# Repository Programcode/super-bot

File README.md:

# Super bot

Super bot (temporary working name) is Adam's passion-project home robot: an indoor mecanum-wheel robot with a creature-style head on a neck (think WALL-E or Vector), a translucent smoked shell, and a layered AI brain that can see, map, talk, fetch, remember, and teach itself new skills.

> **Master page:** the single source of truth is the Grok Bot page **"Super bot"** in Adam's Grok Bot library:
> https://cursor.com/canvas/store-3f866d4b-6e7e-4115-b119-325492ec6c21/45200f5a-d70f-476f-988f-23a206c0bfd9
> (opens for Adam's signed-in account; canvas id `45200f5a-d70f-476f-988f-23a206c0bfd9`).
> A markdown snapshot lives in [`docs/super-bot-page.md`](docs/super-bot-page.md). Pip re-syncs it whenever the page changes.

## Current status (17 Nov 2026)

- **Roadmap layer:** 1 of 6, "Brain on a desk" (laptop + webcam, local YOLO, Qwen mind, Whisper + Piper).
- **Body design:** exploring. AI concept renders are in [`docs/concepts/`](docs/concepts/). Current pick is concept K (WALL-E-style head on a neck, smoked translucent shell).
- **CAD:** starting in Autodesk Fusion. Fusion runs on Adam's Mac; Claude Code on the VPS drives it through Fusion's official MCP server over an SSH tunnel. See [`cad/`](cad/) and the Fusion section of [`CLAUDE.md`](CLAUDE.md).
- **Hardware:** parts plan agreed, mostly not bought yet. Adam owns a Pi 5 8 GB, an ELEGOO UNO kit, and a Circuit Playground Express. No ESP32-S3s yet.
- **Brain:** architecture drafted (mind / controller / reflexes). A full brain plan from Claude Fable is pending review.

Key decisions are in [`docs/decisions.md`](docs/decisions.md).

## The robot in one table

| Part | Plan |
| --- | --- |
| Drive | 80 mm mecanum wheels, 4× JGB37 12 V encoder gear motors, 4× BTS7960 drivers |
| Chassis | Cheap DIY 40×40 cm plate (plywood or aluminium), enclosed in a dense smoked translucent shell |
| Onboard brain | Raspberry Pi 5 8 GB, plus Raspberry Pi AI HAT+ 2 (Hailo-10H) later |
| Real-time | 2× ESP32-S3 (reflexes, motor control at ~1 kHz) |
| Sensors | BNO085 IMU, HC-SR04 ultrasonics, VL53L0X ToF, Logitech C270 webcam, mic |
| Face | 1.3" TFT face on the head |
| Status ring | Circuit Playground Express (10 NeoPixels), also backup tilt / safety |
| Power | 3S 18650 pack |
| Later | Cheap lidar (LD06 / LD19), arm, self-docking charger, custom PCB (v2, KiCad + JLCPCB) |

## Repo layout

```
.
├── CLAUDE.md              Project context for Claude Code (AGENTS.md points here)
├── docs/
│   ├── super-bot-page.md  Snapshot of the Grok Bot master page
│   ├── decisions.md       Decision log (keep current)
│   ├── sync.md            How the page snapshot is kept in sync
│   └── concepts/          AI concept renders (not real photos)
├── cad/                   Fusion designs, STEP/STL exports, Fusion API scripts
├── firmware/
│   ├── esp32/             ESP32-S3 reflex + motor firmware (PlatformIO)
│   └── cpx/               Circuit Playground Express status ring / backup safety
├── pi/                    Onboard brain (Python, later ROS 2)
├── electronics/           Wiring diagrams, future KiCad PCB
├── tests/benchmarks/      Mind benchmarks and test suites
└── scripts/               Helper scripts (ask-pip.sh, sync notes)
```

## License

MIT, see [LICENSE](LICENSE).

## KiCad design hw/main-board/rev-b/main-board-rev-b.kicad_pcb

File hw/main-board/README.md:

# Super bot main board, rev A

The main power and I/O carrier for Super bot v2: one 4-layer board that takes the battery, protects and measures it, makes every supply rail, drives the four wheels, and connects the Raspberry Pi 5 to everything else. The ESP32-S3 on it runs the motor and sensor reflexes. Designed in KiCad 10 on the VPS on 17-18 Nov 2026 by a Claude thread while Adam slept. Nothing has been ordered.

**Status (18 Nov 2026, 05:20 UTC): routed and checked.**
- **ERC:** 0.
- **DRC:** 0 violations and 0 unconnected items, with schematic parity 0. This is the full `kicad-check` gate: severity-all (warnings count), zones refilled, against JLC-safe rules (0.15 mm clearance, 0.10 mm minimum track, 0.3 mm minimum drill, 0.25 mm copper to edge).
- **Two project settings differ from KiCad's defaults:**
  - `lib_footprint_mismatch` is set to ignore, because silkscreen is trimmed per footprint.
  - Minimum thermal-relief spokes is 1 instead of 2, for fine-pitch GND pads in pours.
- **Fab set:** the JLCPCB outputs, STEP and renders are in `out/` and `renders/`.

Read **Open questions** before ordering. The outline is provisional, and three rev A compromises are listed there.

## What's on it

- **Battery input:** XT60 (battery) → 15 A blade fuse → XT30 loop for the DC main switch (or loop key) → reverse-polarity P-MOSFET → 2 mΩ shunt → 12 V bus. TVS on the bus.
- **Battery monitor:** INA226 (I2C 0x40), 16 A full scale, for the time-left model and limp mode.
- **Hardware motor cut (no button):** a retriggerable one-shot only keeps the motors powered while the ESP32 keeps toggling a watchdog pin. An open kill loop or the CPX kill line cuts them too. The cut does two things: it puts all four drivers to sleep and switches off the motor supply with a high-side P-MOSFET.
- **Motors:** 4× DRV8874 in PWM mode. Each limits current at 3.1 A and reports it to an ESP32 ADC (0.82 V/A), and each has an encoder input with pull-ups and RC filters.
- **Rails:**
  - 5.0 V / 6 A for the Pi 5 and 5 V loads (TPS56637), out through a USB-C port.
  - 5.5 V / 6 A servo rail on its own TPS56637.
  - 3.3 V / 1 A logic (AMS1117), which also runs from the ESP32's USB port so you can flash with the battery off.
- **ESP32-S3-WROOM-1-N16R2:** USB-C for programming and debug, BOOT and RST buttons, UART0 to the Pi. The Pi can reset it and put it in bootloader mode itself.
- **TCA9555 I/O expander:** the slow lines (cliff XSHUTs, bumpers, IMU, ultrasonic trigger, fault and status lines).
- **5 V level shifting (74HCT125):** WS2812 LED bar data, both servo signals, ultrasonic trigger. The ultrasonic echo comes back through a divider.
- **Audio:** MAX98357A 3.2 W amp on the Pi's I2S, plus a connector for the INMP441 mic in the head.
- **Connectors:**
  - Pi GPIO (40-way IDC), Pi 5 V out (USB-C), ESP32 USB-C
  - battery XT60, main switch loop XT30
  - 4 motors (JST-XH 6)
  - 4 cliff sensors and the IMU (JST-SH, Qwiic pin order), 2 Qwiic ports (ESP32 bus, Pi bus)
  - bumpers (one PH-6 harness), LED bar, lidar LD19, CPX, kill loop, speaker, mic
  - pan and tilt servos (3-pin 2.54 mm headers), optional HC-SR04 header (not fitted)

## Block diagram

```mermaid
flowchart LR
  BAT["3S4P pack + BMS<br/>10.5-12.6 V"] -->|XT60| FUSE["15 A blade fuse"]
  FUSE -->|XT30 loop| SW["DC main switch<br/>(off board)"]
  SW --> RP["Reverse-polarity<br/>P-FET AOD403"]
  RP --> SH["2 mΩ shunt<br/>INA226"]
  SH --> VBUS(("VBUS 12 V"))
  VBUS --> CUT["Motor cut P-FET<br/>AOD403"]
  CUT --> VMOT(("VMOT"))
  VMOT --> DRV["4x DRV8874<br/>3.1 A limit each"]
  DRV --> MOT["4x JGB37-520<br/>+ encoders"]
  VBUS --> B5["TPS56637<br/>5.0 V 6 A"]
  VBUS --> BS["TPS56637<br/>5.5 V 6 A"]
  B5 -->|USB-C| PI["Raspberry Pi 5<br/>+ AI HAT+ 2"]
  B5 --> LDO["AMS1117<br/>3.3 V"]
  B5 --> L5["LED bar, lidar,<br/>CPX, amp, 74HCT125"]
  BS --> SERVO["Pan/tilt MG90S"]
  LDO --> ESP["ESP32-S3<br/>WROOM-1"]
  USB["USB-C (ESP32)"] -->|VBUS| LDO
  USB <-->|USB| ESP
  WD["74LVC1G123 watchdog<br/>+ kill loop + CPX kill"] -->|MOT_EN| CUT
  WD -->|nSLEEP| DRV
  ESP -->|WDI toggle| WD
  ESP -->|PWM x8| DRV
  DRV -->|IPROPI x4| ESP
  MOT -->|A/B x4| ESP
  ESP <-->|I2C0| EXP["TCA9555"]
  ESP <-->|I2C0| SH
  ESP <-->|I2C0| IMU["BNO085"]
  ESP <-->|I2C1| CLIFF["4x VL53L0X"]
  EXP --> CLIFF
  BUMP["4 bumpers"] --> EXP
  ESP -->|via 74HCT125| SERVO
  ESP -->|via 74HCT125| LED["WS2812 LED bar"]
  ESP -->|UART| CPX["CPX ring"]
  CPX -->|kill| WD
  PI <-->|UART0, EN/BOOT| ESP
  PI <-->|I2S| AMP["MAX98357A"] --> SPK["Speaker"]
  MIC["INMP441"] -->|I2S| PI
  LID["LD19 lidar"] -->|UART2| PI
```

## Why these choices

**Scope (one carrier board, not a Pi HAT).** In the v2 body the Pi 5 + AI HAT+ 2 stands on the spine above this board, so a HAT can't sit on it. One board replaces six things in the v2 CAD: the perfboard driver board, the ESP32 cradle, the cheek power distribution board with its INA226 module, the Pololu Pi buck, the servo buck and the MAX98357A breakout. The Pi connects with two standard cables: a 40-way IDC ribbon from the HAT's pass-through header, and a short USB-C to USB-C cable for 5 V.

**4 layers, not 2.**
- **Layer stack:**
  - In1: an unbroken GND plane under everything (the ESP32 radio, four motor drivers and two 6 A bucks all want one).
  - In2: a split power plane (VMOT under the drivers, 3.3 V under the logic, VBUS as a feed strip, 5 V and the servo rail on the right).
  - Outer layers: signals plus F.Cu/B.Cu pours for the 15 A input path.
- **Why not 2 layers:** on 2 layers the motor and battery currents would share copper with the signal returns, and this many parts would not route in 186 × 70 mm.
- **Cost:** JLC charges roughly EUR 15-20 more for 5 boards of this size, which is small next to the assembly cost.

**Supplies.**
- **The bucks:** the approved Pololu modules (D36V50F5, D36V28F6) became two on-board TI TPS56637 (6 A synchronous, 4.5-28 V in, ceramic-stable D-CAP3).
  - **5 V rail:** it has real headroom for the Pi 5 in 5 A mode plus the LED bar, lidar and amp, and it sits right under the Pi's USB-C.
  - **Servo rail:** it runs on its own converter, so servo stalls never touch the Pi.
  - **Values:** taken from TI's table 4 (5 V: 3.3 µH; above 5 V: 5.6 µH).
  - **Parts and fees:** both rails use the same IC, so there is one Extended fee.
- **3.3 V:** a Basic AMS1117 from 5 V. Its input is diode-ORed with the ESP32's USB VBUS, so the ESP32 can be flashed with no battery and USB never back-feeds the 5 V rail.

**Hardware motor cut.** Adam decided there's no e-stop button on the body. The board still never lets the motors run on software alone:
- **The watchdog:** a 74LVC1G123 one-shot drives MOT_EN high only while the ESP32 keeps toggling WDI from its control loop, at more than 25 Hz (timeout ≈ R·C = 47 kΩ × 1 µF ≈ 47 ms). If the firmware hangs, resets or is being flashed, the motors stop.
- **What MOT_EN switches:** it drives all four DRV8874 nSLEEP pins (outputs go Hi-Z within µs) and the gate of a high-side AOD403 that disconnects VMOT. The FET has a soft turn-on (about 3 ms) so 940 µF of motor bulk capacitance never yanks VBUS.
- **Two more ways to cut:** opening the KILL LOOP connector (a normally-closed loop; fit a shorting plug, a remote-kill relay contact or an NC button later) and the CPX's KILL line.
- **Readback:** the ESP32 reads MOT_EN and the loop state through the expander.
- **Bench use:** JP1 is a solder jumper that bypasses the kill loop.

**Motor drivers.**
- **Mode and current limit:** DRV8874 in **PH/EN mode** (PMODE tied to GND): IN1 = EN (the PWM), IN2 = PH (direction); EN low brakes, nSLEEP low (the motor cut) coasts. PWM (IN/IN) mode was the plan, but PMODE on two drivers couldn't be routed to 3.3 V, and GND sits on the next pin. Firmware just uses the PH/EN truth table. ITRIP = VREF / (R_IPROPI × 455 µA/A) = 2.53 V / (1.8 kΩ × 455 µA/A) ≈ 3.1 A, above the 2.3-2.4 A stall of the 530 rpm JGB37-520, so a stall is limited but never chopped in normal driving.
- **Current sense:** IPROPI goes to ESP32 ADC1 (0.82 V/A) for the stall reflex. A 10 nF filter sits on each IPROPI line, as the datasheet suggests.
- **Fault line:** nFAULT is a wired-OR into the expander, for motors A and B only. Motor C and D nFAULT are left unconnected in rev A because their pins were boxed in during routing. Those drivers still protect themselves (overcurrent auto-retry, thermal shutdown, current limit), and the ESP32 still reads their current through IPROPI. Only the fault flag is missing.
- **Encoders:** they run from 3.3 V, with 10 kΩ pull-ups and 1 kΩ / 1 nF filters. The worst-case edge rate is about 1.8 kHz per channel.

**ESP32 pin budget.**
- **31 free GPIOs, all used:** 8 PWM, 8 encoder (PCNT), 4 ADC, two I2C buses, WDI, the expander INT, LED data, 2 servos, ultrasonic echo, and UART TX to the CPX.
- **Slow lines on the TCA9555:** 4 cliff XSHUTs, 4 bumpers (read on the INT edge, under 1 ms), IMU reset/INT, ultrasonic trigger, the fault/alert lines, MOT_EN and kill readback, and a status LED.
- **Strapping pins:** IO45/IO46 drive the servo buffers with 10 kΩ pull-downs so the chip always boots normally.
- **Module:** -N16R2, because the octal-PSRAM -R8 versions would eat GPIO35-37.

**Pi link.**
- **UART0 to the ESP32's UART0:** that is also its ROM bootloader port, and with GPIO23/24 driving EN and BOOT through 2N7002s the Pi can reflash the ESP32 with esptool, no USB cable needed.
- **Lidar:** the LD19 goes to the Pi's UART2.
- **Audio:** I2S goes to the amp and the mic.
- **I2C:** the Pi's I2C1 has its own Qwiic port; the ESP32 owns its own two buses, so there's no multi-master.
- **Series resistors:** 1 kΩ on every cross-power-domain line stops back-powering when only one side is on.

**Level shifting.** Only where 5 V parts need it:
- **Into 5 V parts:** a 74HCT125 (TTL thresholds, 5 V supply) drives the WS2812 bar, both servo signals and the ultrasonic trigger.
- **From the ultrasonic:** the HC-SR04 echo comes back through a 10k/20k divider.
- **Everything else:** VL53L0X, BNO085, LD19, INMP441, the CPX and the Pi are 3.3 V parts, so they connect directly.

**Parts policy.**
- **Basic first:** every resistor, ceramic capacitor, LED, diode, small FET, switch and the LDO is a JLC Basic or Preferred part (no fee).
- **Extended parts:** these are the ICs, connectors, inductors, shunt and power FETs, for which no Basic part exists.
- **Stock:** every line was checked for stock at more than twice the 5-board need. See the cost table.
- **Footprints:** the module, buck, XT60/XT30, fuse holder, box header, inductors and switches use easyeda2kicad footprints from the LCSC part (so JLC's placement matches); everything else uses KiCad's standard footprints.

## Files

- **Ordering:**
  - `out/JLCPCB/main-board-_JLCPCB_compress.zip`: Gerbers + drill (upload this).
  - `out/fab/jlcpcb/main-board_bom_jlc.csv`: BOM with LCSC numbers.
  - `out/fab/jlcpcb/main-board_cpl_jlc.csv`: placement (CPL).
- **Views:**
  - `renders/pcb-3d-top.png`, `pcb-3d-bottom.png`, `pcb-3d-iso.png`: ray-traced 3D views.
  - `renders/pcb-front.png`, `pcb-back.png`: copper, mask and silkscreen per side.
  - `renders/main-board.step` and `out/3d/main-board-3D.step`: 3D model for Fusion.
- **Schematic:**
  - `renders/main-board-schematic.pdf` / `out/docs/`: schematic, all 10 sheets.
  - `renders/*.png`: one PNG per sheet.
- **Checks:** `reports/main-board-erc.json`, `reports/main-board-drc.json`, `reports/cost.txt`.
- **Sources:**
  - `main-board.kicad_pro` / `.kicad_sch` (root + 6 sheet files) / `.kicad_pcb`: open these in KiCad 10 on the Mac.
  - `lib/`: the project symbol library, footprints and 3D models (self-contained, no global libraries needed except KiCad's own).
  - `gen/`: the generator scripts (below).
  - `jlcpcb.kibot.yaml`: KiBot config for the fab outputs.

## Board

- **Outline and holes:** 186 × 70 mm, 1.6 mm, 4 layers (JLC04161H-7628 stackup), HASL lead-free. 4× M3 plated mounting holes tied to GND. A 24 × 8 mm notch in the top edge leaves room for the cable going into the Pi 5's USB-C port.
- **Where it sits in v2:** flat on spine standoffs in the front chimney, between the front motors (top about z 69) and the Pi 5's bottom edge (z 140). Viewed from the front, the battery/power end is on the robot's right.
- **Provisional:** the outline and hole positions stay provisional until the v2 CAD is final. The CAD still shows the old perfboard and cradle, so it needs a matching board block.
- **Top side only:** all components are on the top, for one-sided JLC assembly. The through-hole parts (XT60, XT30, fuse holder, box header, motor XH, servo headers) need JLC's through-hole soldering.
- **Layers:**
  - F.Cu: parts, signals, and pours for the input chain, VBUS and VMOT.
  - In1: solid GND.
  - In2: split power plane, with VBUS (left and a feed strip), +3V3 (logic area, an encoder band under the motor connectors, and a bridge), VMOT (a 14 mm band under the drivers), +5V (right side up to the Pi USB-C) and VSERVO (under the servo buck and headers).
  - B.Cu: signals, the parallel input-chain pours, the VBUS feed to the bucks, and GND fill.
- **Copper and thermal:**
  - Each DRV8874 exposed pad has 6 thermal vias (0.3 mm drill) into the GND planes.
  - Both MOSFETs sit in their own full-connection pours on both outer layers, stitched with via grids.
  - Every IC has local decoupling. Supply pads that sit over their plane get their own via.
- **Silkscreen:** every connector is labelled (on the four motor XH connectors the label sits along the front lip of the connector's own footprint, the only free spot) (MOTOR A FL ... BATTERY 12V, MAIN SWITCH LOOP, PI 5V OUT, ESP32 USB, PI 5 GPIO, CLIFF F/R/B/L, IMU, QWIIC ESP/PI, BUMPERS, LED BAR, KILL LOOP, LIDAR, CPX, MIC, SPEAKER, PAN, TILT, SONAR, FUSE 15A). Small passives carry their references on the fab layer only, to keep the silkscreen readable.

## Trace widths (IPC-2221, 1 oz outer, 0.5 oz inner)

`python3 gen/calc.py` prints these. The ΔT columns are the temperature rise of the copper.

| Path | Current | Needed on 1 oz outer (ΔT 20 °C) | What the board has |
| --- | --- | --- | --- |
| Battery input chain (fuse rating) | 15 A | 8.3 mm | F.Cu + B.Cu pours in parallel, about 5-8 mm each. **Narrowest point:** the F.Cu VBAT_F strip is crossed by three thin tracks (the LDO's +3V3 link and two signals), so there only the B.Cu strip carries the current, about 4.4 mm net: **≈ 9.5 A at ΔT 20 °C, 11 A at 30 °C** |
| Same, realistic worst case (4 stalls + Pi) | 12.3 A | 6.3 mm | same; fine as a short peak, since stalls are cut within 0.5 s |
| VBUS from the shunt to the motor-cut FET | 10 A | 4.7 mm | 7.8 mm channel on F.Cu and B.Cu |
| VMOT to the drivers (normal driving) | 4 A | 1.3 mm | pours at the FET, then a 14 mm In2 band (6 A at ΔT 20 °C, 7 A at 30 °C) |
| One motor output (current limit) | 3.1 A | 0.94 mm | 1.0 mm, with a 0.4 mm neck for 1.1 mm at the 0.65 mm-pitch pin |
| VBUS feed to both bucks | 3.8 A | 1.24 mm | 1.5 mm B.Cu feed, 0.8 mm drop to each VIN, plus a local VIN pour |
| +5 V to the Pi | 6 A | 2.3 mm | In2 5 V plane, 18-37 mm wide (7 A at ΔT 20 °C), plus a pour and 4 vias at the Pi USB-C |
| Servo rail | 2 A | 0.5 mm | In2 servo plane |

Honest limits:
- **VMOT band:** 10 A (all four motors stalled at once) would need 28 mm of 0.5 oz inner copper. The band is 14 mm. That's fine because stalls are limited to 3.1 A per motor by the drivers and cut by the ESP32 within 0.5 s, so the full 10 A only lasts for moments.
- **Input chain rating:** this board is good for about 10 A continuous on the input chain (typical draw is 3-5 A), not the full 15 A fuse rating. The fuse still protects the wiring against a short. Rev B: keep the input, VBUS and VMOT pours free of other nets. The autorouter ran some signals and the +5V/VSERVO feeds through them, so the pours are perforated (VBUS B.Cu is in 6 pieces, stitched together by vias and the In2 strip).
- **Thin power links:** the LDO output reaches the main 3.3 V plane through a 0.15 mm stretch, good for about 0.8 A. The 3.3 V rail needs under 0.7 A even with ESP32 Wi-Fi bursts, but widen it in rev B.
- **Last-mile links:** a few decoupling-capacitor, divider and second-input-capacitor connections on VBUS, VMOT and +3V3 are 0.15-0.4 mm tracks. None carries a main current, but the second buck input caps (C105, C115) sit on long thin links and add little decoupling. The VIN-side caps C104 and C113 are the real input caps.

## Ordering at JLCPCB

1. Upload `out/JLCPCB/main-board-_JLCPCB_compress.zip` as the Gerber.
   - Set 4 layers, 1.6 mm, JLC04161H-7628 impedance stack (or "no requirement").
   - Choose HASL lead-free, green or black mask, 5 pcs.
2. Turn on PCB Assembly: standard, top side, 5 boards.
   - Upload `out/fab/jlcpcb/main-board_bom_jlc.csv` (BOM) and `main-board_cpl_jlc.csv` (CPL).
3. In JLC's placement preview, check the rotation of:
   - the ESP32 module (antenna end flush with the top edge, over the copper keepout)
   - both TPS56637 (pin 1 dot)
   - the DRV8874s, USB-C connectors, the INA226, TCA9555, 74HCT125 and 74LVC1G123
   - the electrolytics (stripe = minus)
   - the SMBJ15A TVS diodes (band toward VBUS/VMOT)
4. Through-hole parts (XT60, XT30, fuse holder, box header, motor XH, servo headers): choose JLC's THT soldering, or leave them out and solder them yourself.
5. The optional HC-SR04 header (J415) and the kill-loop solder jumper (JP201) are not fitted.
6. PCBWay takes the same Gerber zip. Its BOM needs the columns Designator, Qty, MPN and Package: build it from `out/fab/jlcpcb/main-board_bom_jlc.csv` (LCSC numbers are in the BOM).

## Cost estimate for 5 assembled boards

`python3 gen/cost.py 5` prices every BOM line at the 5-board quantity from the JLC catalog snapshot, or the live LCSC API for the ESP32 module, and checks that stock is at least twice the need.

| Item | USD | EUR |
| --- | --- | --- |
| PCB: 5× 186 × 70 mm, 4-layer, 1.6 mm, HASL (JLC quote estimate) | 32 | 29 |
| Parts: 65 BOM lines, 225 placed parts per board | 157 | 145 |
| Assembly: setup + stencil + 675 SMT and 82 THT joints per board | 38 | 35 |
| Extended part fees: 27 × $3 | 81 | 75 |
| Shipping to Hungary (estimate, before VAT and customs) | 20 | 18 |
| **Total for 5 assembled boards** | **328** | **≈ 300 (about 60 per board)** |

Assumptions:
- USD → EUR at 0.92.
- Prices are from the 17 Nov 2026 snapshot. Check the final number in JLC's quote.
- Hungarian VAT (27 %) and any customs fee are on top.

Biggest costs:
- the four DRV8874s ($17.6)
- the two TPS56637s ($22.5)
- the ESP32 module ($26.4)
- Extended part fees

Going cheaper:
- Swap the TI SN74LVC1G123 for the JSM clone (C53114387, saves about $7).
- Do the through-hole soldering yourself.

## Open questions for Adam

0. **Rev A compromises, all small, chosen to finish the routing:**
   - The DRV8874s run in PH/EN mode, not PWM mode.
   - Motor C/D nFAULT is not wired.
   - The motor-cut gate pull-up R207 sits next to C206.

   All three are in the schematic, so schematic and board match. Rev B can route nFAULT C/D if the board grows by about 5 mm or the passives move to the bottom side.
1. **On-board bucks instead of the Pololu modules.** The approved D36V50F5 / D36V28F6 modules are replaced by two TI TPS56637 on the board. OK? Going back means adding two 3-pin headers and deleting the buck blocks.
2. **v2 CAD fit.** The board is 186 × 70 mm, from the front motors (z ≈ 70) up to the Pi's bottom edge (z = 140). The Pi's USB-C cable needs the notch and a right-angle plug: either use a short right-angle USB-C cable, or raise `pi_z0` by about 8 mm in v2. The v2 CAD still shows the perfboard, the ESP32 cradle, the cheek PDB/INA226, the Pololu bucks and the amp breakout; all of those are now on this board.
3. **Fuse.** v2 puts a 15 A blade fuse on the pack and this board has one too. Keep both (harmless) or drop the pack one? Check which blade size the XF-506P holder takes (standard ATO/ATC is expected; the LCSC datasheet is an image) before buying fuses.
4. **Motor and encoder wiring.** J601-J901 follow the common JGB37-520 6-wire order: M+, GND, A, B, VCC, M-. The encoders run at 3.3 V. Check this against the motors you buy, and that their Hall sensors work at 3.3 V (most do; if not, it's a small change).
5. **XT60 polarity.** The board takes pad 2 as + (the footprint's silkscreen mark). Reverse-polarity protection means a mistake won't damage anything, but check against the real part before soldering cables.
6. **Kill loop.** It's normally closed. With nothing plugged in, the motors stay off (fail-safe). Fit a shorting plug, or bridge JP201 on the bench. Do you want a remote kill or a button on it later?
7. **Pi 5 power.** A USB-C to USB-C cable rated 5 A, or a short right-angle 3 A one, from PI 5V OUT. Set `usb_max_current_enable=1` in config.txt. The port advertises 3 A (Rp = 10 kΩ) and can't do USB-PD.
8. **Second ESP32.** There's no footprint for one. The Qwiic port on the ESP32's I2C1 and the Pi's UARTs leave room for later. OK?
9. **Speaker and mic.** MAX98357A gain is 9 dB into 4 Ω, and the mic is on the left I2S channel. Check that the head's 6-wire mic cable through the neck works at about 3 MHz BCLK (33 Ω terminations are fitted).
10. **Bench checks before trusting the watchdog:** the one-shot timeout (≈ 47 ms) and that the ESP32 firmware toggles WDI at 100 Hz or more.

## Not verified

- No SPICE or thermal simulation. The buck values follow TI's tables.
- The current-limit, watchdog and motor-cut behaviour are calculated, not tested on hardware.
- **Routing:** it was done by Freerouting plus small custom helpers (`gen/fixup.py` grid router, `gen/ripup.py`). A few last-mile links are 0.15 mm tracks, and some cut through the F.Cu copy of a power pour (its B.Cu twin carries the current). DRC passes, but have a human look over the copper in KiCad before ordering, especially around the motor drivers and the bucks.
- The JLC placement rotations are untested until the online preview.
- The 3D models for the module, buck, XT60/XT30, fuse holder, box header, inductors and switches come from LCSC/EasyEDA. The other parts use KiCad's library models.
- Fit in the v2 body is checked against `cad/v2/README.md` parameters only. The CAD isn't updated (another thread owns Fusion).

## How it was made (and how to change it)

Everything is generated from Python, so a change is an edit plus a re-run, not hand-editing KiCad files:

1. `gen/design.py` holds the whole circuit: every part, its LCSC number and its nets, one function per sheet. `gen/symbols.py` makes the project symbols KiCad lacks (DRV8874, TPS56637, AOD403 with DPAK numbering, XT60/XT30 with mount pins, MAX98357A with the pad typed passive).
2. `gen/build_sch.py` writes the hierarchical schematic (root + power, motor cut, MCU, I/O, audio, and one motor-channel sheet used four times) and the project file with the net classes.
3. `gen/build_pcb.py` builds the board from the netlist. It hand-places the key parts (connectors, ICs, power parts) and packs each part's passives around the pin they connect to, inside that block's area.
4. `gen/route.py` draws the planes and power pours. It also draws the locked high-current tracks (motor outputs, buck SW nodes, VBUS feed, driver VM vias, exposed-pad thermal vias) and places its own via fanout for every supply pad that sits over its plane. Then it exports Specctra DSN (inner layers as planes), runs Freerouting 2.5, imports the result and fills the zones. `--continue` re-runs Freerouting on an already-routed board.
5. `gen/patch.py` makes targeted copper fixes after routing: the +3V3 In2 bridge, buck VIN pours, the Pi USB-C 5 V pour and vias, and the buck AGND-PGND ties.
6. `gen/fixup.py` is a small grid A* router (0.05 mm grid, F.Cu/B.Cu plus vias) for the last connections Freerouting leaves open.
7. `gen/clean_loop.sh` runs `gen/cleanup.py` until nothing changes. It removes dangling or duplicate vias and dangling stubs. pcbnew's Python API breaks after `Remove()`, so it runs one round per process.
8. `gen/finish.py` places the connector labels where they don't hit copper or other silk, and trims footprint silk segments that land on pads or the edge (they move to the fab layer). Because of that trim, `lib_footprint_mismatch` is set to ignore in the project; every manufacturing check stays at its default. It also writes the JLC04161H-7628 stackup.
9. `gen/cost.py` re-checks stock and prices every BOM line; `gen/calc.py` does the trace-width maths.

Run them in that order from `hw/main-board` (route, then patch, fixup, clean_loop, finish, clean_loop) with `~/tools/kicad-mcp-server/.venv/bin/python` (it has `sexpdata` and pcbnew). Then use the helpers: `kicad-check main-board.kicad_pcb`, `kicad-render main-board.kicad_pcb`, `kicad-jlc .`.

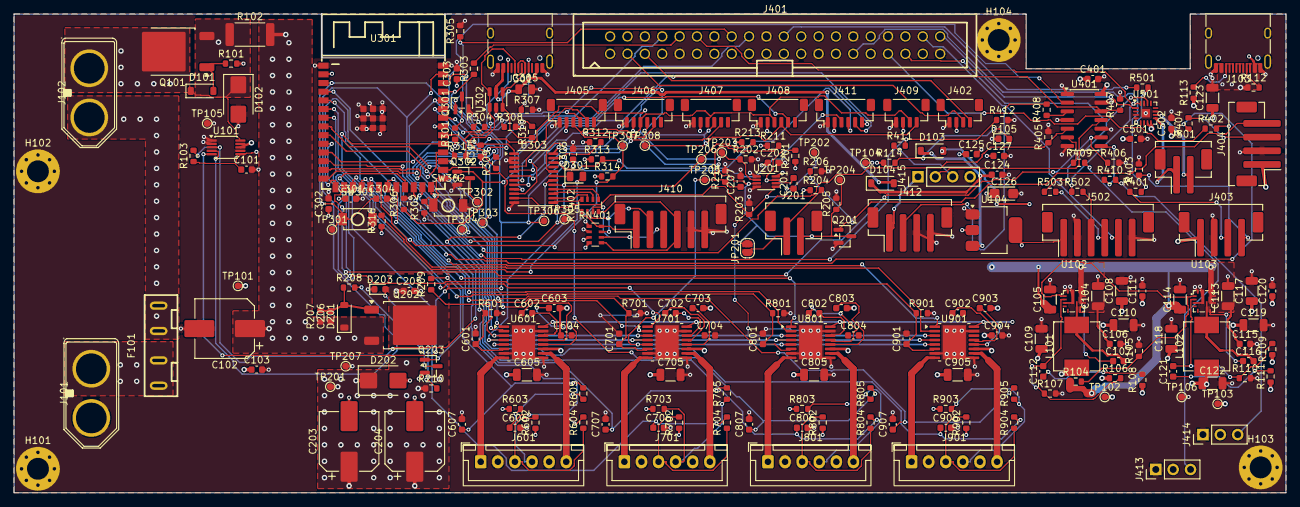
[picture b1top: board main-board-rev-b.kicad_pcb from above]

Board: 4 copper layers, 186.0 x 70.0 mm, 237 parts (0 on the bottom side), 153 nets.

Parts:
C101, C103, C106, C107, C111, C115, C116, C120, C127, C202, C205, C207, C302, C303, C306, C401, C502, C603, C604, C703, C704, C803, C804, C903, C904: 100nF 50V X7R; C_0603_1608Metric
C102, C203, C204: 470uF 35V 8x10.5; CP_Elec_8x10.5
C104, C105, C113, C114, C605, C705, C805, C905: 10uF 50V X5R; C_1206_3216Metric
C108, C109, C110, C117, C118, C119, C122, C123: 22uF 25V X5R; C_1206_3216Metric
C112, C121: 100pF 50V C0G; C_0603_1608Metric
C124, C501: 10uF 25V X5R; C_0603_1608Metric
C125, C301: 22uF 6.3V X5R; C_0603_1608Metric
C126: 10uF 16V tantalum; CP_EIA-3216-18_Kemet-A
C201, C206, C304: 1uF 50V X5R; C_0603_1608Metric
C305: 4.7uF 25V X5R; C_0805_2012Metric
C601, C701, C801, C901: 10nF 50V X7R; C_0603_1608Metric
C602, C702, C802, C902: 22nF 50V X7R; C_0603_1608Metric
C606, C607, C706, C707, C806, C807, C906, C907: 1nF 50V X7R; C_0603_1608Metric
D101, D201: BZT52C15; D_SOD-123
D102, D202: SMBJ15A; D_SMB
D103, D104: B5819W; D_SOD-123
D105, D203: Red; LED_0603_1608Metric
D301: Green; LED_0805_2012Metric
F101: 15A blade (XF-506P holder); FUSE-TH_XF-506P
H101, H102, H103, H104: M3; MountingHole_3.2mm_M3_Pad_Via
J101: BAT IN XT60PB-M (vertical); CONN-TH_XT60PB-M
J102: MAIN SWITCH XT60PB-M (vertical); CONN-TH_XT60PB-M
J103: PI 5V OUT; USB_C_Receptacle_HRO_TYPE-C-31-M-12
J201: KILL LOOP; JST_PH_B2B-PH-SM4-TB_1x02-1MP_P2.00mm_Vertical
J301: ESP32 USB; USB_C_Receptacle_HRO_TYPE-C-31-M-12
J401: PI GPIO; IDC-TH_40P-P2.54_C9138
J402: QWIIC PI; JST_SH_BM04B-SRSS-TB_1x04-1MP_P1.00mm_Vertical
J403: LIDAR; JST_PH_B4B-PH-SM4-TB_1x04-1MP_P2.00mm_Vertical
J404: CPX; JST_PH_B4B-PH-SM4-TB_1x04-1MP_P2.00mm_Vertical
J405: CLIFF 1; JST_SH_BM06B-SRSS-TB_1x06-1MP_P1.00mm_Vertical
J406: CLIFF 2; JST_SH_BM06B-SRSS-TB_1x06-1MP_P1.00mm_Vertical
J407: CLIFF 3; JST_SH_BM06B-SRSS-TB_1x06-1MP_P1.00mm_Vertical
J408: CLIFF 4; JST_SH_BM06B-SRSS-TB_1x06-1MP_P1.00mm_Vertical
J409: QWIIC ESP; JST_SH_BM04B-SRSS-TB_1x04-1MP_P1.00mm_Vertical
J410: BUMPERS; JST_PH_B6B-PH-SM4-TB_1x06-1MP_P2.00mm_Vertical
J411: IMU; JST_SH_BM06B-SRSS-TB_1x06-1MP_P1.00mm_Vertical
J412: LED BAR; JST_PH_B4B-PH-SM4-TB_1x04-1MP_P2.00mm_Vertical
J413: PAN SERVO; PinHeader_1x03_P2.54mm_Vertical
J414: TILT SERVO; PinHeader_1x03_P2.54mm_Vertical
J415: HC-SR04 (optional); PinHeader_1x04_P2.54mm_Vertical
J501: SPEAKER; JST_PH_B2B-PH-SM4-TB_1x02-1MP_P2.00mm_Vertical
J502: MIC; JST_PH_B6B-PH-SM4-TB_1x06-1MP_P2.00mm_Vertical
J601, J701, J801, J901: MOTOR; JST_XH_B6B-XH-A_1x06_P2.50mm_Vertical
JP201: KILL BYPASS; SolderJumper-2_P1.3mm_Open_RoundedPad1.0x1.5mm
L101, L102: 3.3uH; IND-SMD_L7.0-W6.6_FXL0630
Q101, Q202: AOD403; TO-252-2
Q201, Q203, Q301, Q302: 2N7002; SOT-23
R101, R103, R112, R113, R207, R211, R213, R301, R302, R311, R403, R405, R406, R407, R411, R602, R603, R702, R703, R802, R803, R902, R903: 10k; R_0603_1608Metric
R102: 2m 1% 3W 2512; R_2512_6332Metric
R104, R202, R203, R205, R206, R305, R306: 100k; R_0603_1608Metric
R105, R108, R111, R412: 20k; R_0603_1608Metric
R106, R109: 22k; R_0603_1608Metric
R107, R110: 3k; R_0603_1608Metric
R114, R204, R303, R304, R316, R401, R402, R404, R604, R605, R704, R705, R804, R805, R904, R905: 1k; R_0603_1608Metric
R201: 47k; R_0603_1608Metric
R208, R210, R312, R313: 4.7k; R_0603_1608Metric
R209: 100; R_0603_1608Metric
R212: 33k; R_0603_1608Metric
R307, R308: 5.1k; R_0603_1608Metric
R309, R310: 22; R_0603_1608Metric
R314, R315: 2.2k; R_0603_1608Metric
R408, R409, R410: 330; R_0603_1608Metric
R501: 470k; R_0603_1608Metric
R502, R503: 33; R_0603_1608Metric
R601, R701, R801, R901: 1.8k; R_0603_1608Metric
RN401: 4x10k; R_Array_Convex_4x0603
RN402: 4x1k; R_Array_Convex_4x0603
SW301: RESET; SW-SMD_L3.9-W3.0-P4.45
SW302: BOOT; SW-SMD_L3.9-W3.0-P4.45
TP101: VBUS; TestPoint_Pad_D1.0mm
TP102: 5V; TestPoint_Pad_D1.0mm
TP103: VSERVO; TestPoint_Pad_D1.0mm
TP104: 3V3; TestPoint_Pad_D1.0mm
TP105, TP106, TP207: GND; TestPoint_Pad_D1.0mm
TP201: VMOT; TestPoint_Pad_D1.0mm
TP202: MOT EN; TestPoint_Pad_D1.0mm
TP203: WDI; TestPoint_Pad_D1.0mm
TP204: CUT OK; TestPoint_Pad_D1.0mm
TP205: VREF; TestPoint_Pad_D1.0mm
TP206: MOT NFAULT; TestPoint_Pad_D1.0mm
TP301: ESP EN; TestPoint_Pad_D1.0mm
TP302: ESP IO0; TestPoint_Pad_D1.0mm
TP303: ESP TXD0; TestPoint_Pad_D1.0mm
TP304: ESP RXD0; TestPoint_Pad_D1.0mm
TP305: I2C0 SDA; TestPoint_Pad_D1.0mm
TP306: I2C0 SCL; TestPoint_Pad_D1.0mm
TP307: I2C1 SDA; TestPoint_Pad_D1.0mm
TP308: I2C1 SCL; TestPoint_Pad_D1.0mm
U101: INA226AIDGSR; MSOP-10_3x3mm_P0.5mm
U102, U103: TPS56637RPAR; VQFN-HR-10_L3.0-W3.0_RPA
U104: AMS1117-3.3; SOT-223-3_TabPin2
U201: 74LVC1G123DC (JSM); VSSOP-8_2.3x2mm_P0.5mm
U301: ESP32-S3-WROOM-1-N16R2; WIRELM-SMD_ESP32-S3-WROOM-1
U302: SRV05-4; SOT-23-6
U303: TCA9555PWR; TSSOP-24_4.4x7.8mm_P0.65mm
U401: 74HCT125D; SOIC-14_3.9x8.7mm_P1.27mm
U501: MAX98357AETE+T; TQFN-16-1EP_3x3mm_P0.5mm_EP1.23x1.23mm
U601, U701, U801, U901: DRV8874PWPR; HTSSOP-16-1EP_4.4x5mm_P0.65mm_EP3.4x5mm_Mask2.46x2.31mm

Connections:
+3V3: C101.1, C125.1, C126.1, C127.1, C202.1, C301.1, C302.1, C303.1, C306.1, J402.2, J405.2, J406.2, J407.2, J408.2, J409.2, J411.2, J502.1, J601.5, J701.5, J801.5, J901.5, R103.1, R114.1, R201.1, R204.1, R211.1, R213.1, R301.1, R302.1, R311.1, R312.1, R313.1, R314.1, R315.1, R316.1, R602.1, R603.1, R702.1, R703.1, R802.1, R803.1, R902.1, R903.1, RN401.1, RN401.2, RN401.3, RN401.4, TP104.1, U101.6, U104.2, U201.8, U301.2, U303.24, U601.16, U701.16, U801.16, U901.16
+5V: C108.1, C109.1, C110.1, C111.1, C123.1, C401.1, C501.1, C502.1, D103.2, J103.A4, J103.A9, J103.B4, J103.B9, J403.1, J404.1, J412.1, J415.1, L101.2, R106.1, R108.1, R112.1, R113.1, TP102.1, U401.14, U501.7, U501.8
+5V_USB: C305.1, D104.2, J301.A4, J301.A9, J301.B4, J301.B9, U302.5
/AMP_SD: J401.22, R501.1
/Audio/AMP_SDM: R501.2, U501.4
/Audio/MIC_SCK: J502.3, R502.2
/Audio/MIC_WS: J502.4, R503.2
/Audio/SPK_N: J501.2, U501.10
/Audio/SPK_P: J501.1, U501.9
/BUMP1: RN402.8, U303.13
/BUMP2: RN402.7, U303.14
/BUMP3: RN402.6, U303.15
/BUMP4: RN402.5, U303.16
/CLIFF1_XSHUT: J405.5, U303.4
/CLIFF2_XSHUT: J406.5, U303.5
/CLIFF3_XSHUT: J407.5, U303.6
/CLIFF4_XSHUT: J408.5, U303.7
/CPX_KILL: J404.4, Q201.1, R206.1
/CPX_TX: R404.1, U301.15
/CUT_OK: J201.2, JP201.2, Q201.3, R205.1, TP204.1, U201.3, U303.20
/HC_ECHO_3V3: R411.2, R412.1, U301.12
/HC_TRIG_3V3: R407.1, U303.10, U401.12
/I2C0_SCL: J411.4, R313.2, TP306.1, U101.5, U301.38, U303.22
/I2C0_SDA: J411.3, R312.2, TP305.1, U101.4, U301.39, U303.23
/I2C1_SCL: J405.4, J406.4, J407.4, J408.4, J409.4, R315.2, TP308.1, U301.32
/I2C1_SDA: J405.3, J406.3, J407.3, J408.3, J409.3, R314.2, TP307.1, U301.31
/I2S_BCLK: J401.12, R502.1, U501.16
/I2S_DIN: J401.38, J502.5
/I2S_DOUT: J401.40, U501.1
/I2S_LRCLK: J401.35, R503.1, U501.14
/IMU_INT: J411.5, U303.9
/IMU_RST: J411.6, U303.8
/INA_ALERT: R103.2, U101.3, U303.18
/IO/BUMP1_RAW: J410.1, RN401.8, RN402.1
/IO/BUMP2_RAW: J410.2, RN401.7, RN402.2
/IO/BUMP3_RAW: J410.3, RN401.6, RN402.3
/IO/BUMP4_RAW: J410.4, RN401.5, RN402.4
/IO/CPX_RX: J404.3, R404.2
/IO/HC_ECHO: J415.3, R411.1
/IO/HC_TRIG: J415.2, U401.11
/IO/LED_DATA: J412.2, R408.2
/IO/LED_DATA_B: R408.1, U401.3
/IO/LIDAR_PWM: J403.4, R402.2, R403.1
/IO/LIDAR_TX: J403.3, R401.1
/IO/PI_LIDAR_PWM: J401.33, R402.1
/IO/PI_LIDAR_RX: J401.29, R401.2
/IO/PI_SCL: J401.5, J402.4
/IO/PI_SDA: J401.3, J402.3
/IO/SERVO1_B: R409.1, U401.6
/IO/SERVO1_SIG: J413.3, R409.2
/IO/SERVO2_B: R410.1, U401.8
/IO/SERVO2_SIG: J414.3, R410.2
/LED_DATA_3V3: U301.35, U401.2
/M1_ENC_A: C606.1, R604.2, U301.21
/M1_ENC_B: C607.1, R605.2, U301.22
/M1_IN1: U301.8, U601.1
/M1_IN2: U301.9, U601.2
/M1_IPROPI: C601.1, R601.1, U301.4, U601.6
/M2_ENC_A: C706.1, R704.2, U301.23
/M2_ENC_B: C707.1, R705.2, U301.24
/M2_IN1: U301.10, U701.1
/M2_IN2: U301.11, U701.2
/M2_IPROPI: C701.1, R701.1, U301.5, U701.6
/M3_ENC_A: C806.1, R804.2, U301.25
/M3_ENC_B: C807.1, R805.2, U301.28
/M3_IN1: U301.17, U801.1
/M3_IN2: U301.18, U801.2
/M3_IPROPI: C801.1, R801.1, U301.6, U801.6
/M4_ENC_A: C906.1, R904.2, U301.29
/M4_ENC_B: C907.1, R905.2, U301.30
/M4_IN1: U301.19, U901.1
/M4_IN2: U301.20, U901.2
/M4_IPROPI: C901.1, R901.1, U301.7, U901.6
/MCU/ESP_EN: C304.1, Q301.3, R301.2, SW301.1, TP301.1, U301.3
/MCU/ESP_IO0: Q302.3, R302.2, SW302.1, TP302.1, U301.27
/MCU/ESP_RXD0: R304.2, TP304.1, U301.36
/MCU/ESP_TXD0: R303.1, TP303.1, U301.37
/MCU/EXP_INT: R311.2, U301.34, U303.1
/MCU/LED_STATUS: D301.1, U303.19
/MCU/LED_STATUS_A: D301.2, R316.2
/MCU/USB_CC1: J301.A5, R307.1
/MCU/USB_CC2: J301.B5, R308.1
/MCU/USB_C_DN: J301.A7, J301.B7, R310.1, U302.3, U302.4
/MCU/USB_C_DP: J301.A6, J301.B6, R309.1, U302.1, U302.6
/MCU/USB_DN: R310.2, U301.13
/MCU/USB_DP: R309.2, U301.14
/MOT_EN: R203.1, R209.1, TP202.1, U201.5, U303.11, U601.3, U701.3, U801.3, U901.3
/MOT_NFAULT: R213.2, TP206.1, U303.17, U601.4, U701.4, U801.4, U901.4
/Motor A (front left)/CPH: C602.1, U601.13
/Motor A (front left)/CPL: C602.2, U601.14
/Motor A (front left)/ENC_A_RAW: J601.3, R602.2, R604.1
/Motor A (front left)/ENC_B_RAW: J601.4, R603.2, R605.1
/Motor A (front left)/OUT1: J601.1, U601.8
/Motor A (front left)/OUT2: J601.6, U601.10
/Motor A (front left)/VCP: C603.1, U601.12
/Motor B (front right)/CPH: C702.1, U701.13
/Motor B (front right)/CPL: C702.2, U701.14
/Motor B (front right)/ENC_A_RAW: J701.3, R702.2, R704.1
/Motor B (front right)/ENC_B_RAW: J701.4, R703.2, R705.1
/Motor B (front right)/OUT1: J701.1, U701.8
/Motor B (front right)/OUT2: J701.6, U701.10
/Motor B (front right)/VCP: C703.1, U701.12
/Motor C (rear left)/CPH: C802.1, U801.13
/Motor C (rear left)/CPL: C802.2, U801.14
/Motor C (rear left)/ENC_A_RAW: J801.3, R802.2, R804.1
/Motor C (rear left)/ENC_B_RAW: J801.4, R803.2, R805.1
/Motor C (rear left)/OUT1: J801.1, U801.8
/Motor C (rear left)/OUT2: J801.6, U801.10
/Motor C (rear left)/VCP: C803.1, U801.12
/Motor D (rear right)/CPH: C902.1, U901.13
/Motor D (rear right)/CPL: C902.2, U901.14
/Motor D (rear right)/ENC_A_RAW: J901.3, R902.2, R904.1
/Motor D (rear right)/ENC_B_RAW: J901.4, R903.2, R905.1
/Motor D (rear right)/OUT1: J901.1, U901.8
/Motor D (rear right)/OUT2: J901.6, U901.10
/Motor D (rear right)/VCP: C903.1, U901.12
/Motor cut/KILL_SRC: J201.1, JP201.1, R204.2
/Motor cut/LED_VMOT: D203.2, R210.2
/Motor cut/MC_D: Q203.3, R208.2
/Motor cut/MC_EN: Q203.1, R209.2
/Motor cut/MC_G: C206.2, D201.2, Q202.1, R207.2, R208.1
/Motor cut/WD_CX: C201.2, U201.6
/Motor cut/WD_RC: C201.1, R201.2, U201.7
/PI_ESP_BOOT: J401.18, Q302.1, R306.1
/PI_ESP_EN: J401.16, Q301.1, R305.1
/PI_RXD: J401.10, R303.2
/PI_TXD: J401.8, R304.1
/Power/BUCK5_BOOT: C107.1, U102.7
/Power/BUCK5_FB: C112.2, R106.2, R107.1, U102.2
/Power/BUCK5_FF: C112.1, R108.2
/Power/BUCK5_SW: C107.2, L101.1, U102.6
/Power/BUCKS_BOOT: C116.1, U103.7
/Power/BUCKS_FB: C121.2, R109.2, R110.1, U103.2
/Power/BUCKS_FF: C121.1, R111.2
/Power/BUCKS_SW: C116.2, L102.1, U103.6
/Power/BUCK_EN: R104.2, R105.1, U102.1, U103.1
/Power/LED_3V3: D105.2, R114.2
/Power/PIPWR_CC1: J103.A5, R112.2
/Power/PIPWR_CC2: J103.B5, R113.2
/Power/RP_G: D101.2, Q101.1, R101.1
/Power/VBAT_F: F101.2, J102.2
/Power/VBAT_IN: F101.1, J101.1
/Power/VPROT: D101.1, D102.1, Q101.3, R102.1, U101.10
/Power/VSW: J102.1, Q101.2
/SERVO1_3V3: R405.1, U301.26, U401.5
/SERVO2_3V3: R406.1, U301.16, U401.9
/VREF: C207.1, R211.2, R212.1, TP205.1, U601.5, U701.5, U801.5, U901.5
/WDI: R202.1, TP203.1, U201.2, U301.33
GND: C101.2, C102.2, C103.2, C104.2, C105.2, C106.2, C108.2, C109.2, C110.2, C111.2, C113.2, C114.2, C115.2, C117.2, C118.2, C119.2, C120.2, C122.2, C123.2, C124.2, C125.2, C126.2, C127.2, C202.2, C203.2, C204.2, C205.2, C207.2, C301.2, C302.2, C303.2, C304.2, C305.2, C306.2, C401.2, C501.2, C502.2, C601.2, C604.2, C605.2, C606.2, C607.2, C701.2, C704.2, C705.2, C706.2, C707.2, C801.2, C804.2, C805.2, C806.2, C807.2, C901.2, C904.2, C905.2, C906.2, C907.2, D102.2, D105.1, D202.2, D203.1, H101.1, H102.1, H103.1, H104.1, J101.2, J103.A1, J103.A12, J103.B1, J103.B12, J103.SH, J301.A1, J301.A12, J301.B1, J301.B12, J301.SH, J401.6, J401.9, J401.14, J401.20, J401.25, J401.30, J401.34, J401.39, J402.1, J403.2, J404.2, J405.1, J406.1, J407.1, J408.1, J409.1, J410.5, J410.6, J411.1, J412.3, J412.4, J413.1, J414.1, J415.4, J502.2, J502.6, J601.2, J701.2, J801.2, J901.2, Q201.2, Q203.2, Q301.2, Q302.2, R101.2, R105.2, R107.2, R110.2, R202.2, R203.2, R205.2, R206.2, R212.2, R305.2, R306.2, R307.2, R308.2, R403.2, R405.2, R406.2, R407.2, R412.2, R601.2, R701.2, R801.2, R901.2, SW301.2, SW302.2, TP105.1, TP106.1, TP207.1, U101.1, U101.2, U101.7, U102.3, U102.9, U102.10, U103.3, U103.9, U103.10, U104.1, U201.1, U201.4, U301.1, U301.40, U301.41, U302.2, U303.2, U303.3, U303.12, U303.21, U401.1, U401.4, U401.7, U401.10, U401.13, U501.3, U501.11, U501.15, U501.17, U601.7, U601.9, U601.15, U601.17, U701.7, U701.9, U701.15, U701.17, U801.7, U801.9, U801.15, U801.17, U901.7, U901.9, U901.15, U901.17
V3V3_IN: C124.1, D103.1, D104.1, U104.3
VBUS: C102.1, C103.1, C104.1, C105.1, C106.1, C113.1, C114.1, C115.1, C206.1, D201.1, Q202.3, R102.2, R104.1, R207.1, TP101.1, U101.8, U101.9, U102.8, U103.8
VMOT: C203.1, C204.1, C205.1, C603.2, C604.1, C605.1, C703.2, C704.1, C705.1, C803.2, C804.1, C805.1, C903.2, C904.1, C905.1, D202.1, Q202.2, R210.1, TP201.1, U601.11, U701.11, U801.11, U901.11
VSERVO: C117.1, C118.1, C119.1, C120.1, C122.1, J413.2, J414.2, L102.2, R109.1, R111.1, TP103.1

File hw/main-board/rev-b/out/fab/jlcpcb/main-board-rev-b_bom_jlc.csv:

"Comment","Designator","Footprint","LCSC Part #"
"100pF 50V C0G","C112,C121","C_0603_1608Metric","C14858"
"1nF 50V X7R","C606,C607,C706,C707,C806,C807,C906,C907","C_0603_1608Metric","C1588"
"10nF 50V X7R","C601,C701,C801,C901","C_0603_1608Metric","C57112"
"22nF 50V X7R","C602,C702,C802,C902","C_0603_1608Metric","C21122"
"100nF 50V X7R","C101,C103,C106,C107,C111,C115,C116,C120,C127,C202,C205,C207,C302,C303,C306,C401,C502,C603,C604,C703,C704,C803,C804,C903,C904","C_0603_1608Metric","C14663"
"1uF 50V X5R","C201,C206,C304","C_0603_1608Metric","C15849"
"4.7uF 25V X5R","C305","C_0805_2012Metric","C1779"
"10uF 50V X5R","C104,C105,C113,C114,C605,C705,C805,C905","C_1206_3216Metric","C13585"
"10uF 25V X5R","C124,C501","C_0603_1608Metric","C96446"
"10uF 16V tantalum","C126","CP_EIA-3216-18_Kemet-A","C7171"
"22uF 25V X5R","C108,C109,C110,C117,C118,C119,C122,C123","C_1206_3216Metric","C12891"
"22uF 6.3V X5R","C125,C301","C_0603_1608Metric","C59461"
"470uF 35V 8x10.5","C102,C203,C204","CP_Elec_8x10.5","C48935389"
"B5819W","D103,D104","D_SOD-123","C8598"
"BZT52C15","D101,D201","D_SOD-123","C19077412"
"Green","D301","LED_0805_2012Metric","C2297"
"Red","D105,D203","LED_0603_1608Metric","C2286"
"SMBJ15A","D102,D202","D_SMB","C19077569"
"BUMPERS","J410,J502","JST_PH_B6B-PH-SM4-TB_1x06-1MP_P2.00mm_Vertical","C471518"
"CLIFF 1","J405,J406,J407,J408,J411","JST_SH_BM06B-SRSS-TB_1x06-1MP_P1.00mm_Vertical","C160392"
"KILL LOOP","J201,J501","JST_PH_B2B-PH-SM4-TB_1x02-1MP_P2.00mm_Vertical","C160352"
"LIDAR","J403,J404,J412","JST_PH_B4B-PH-SM4-TB_1x04-1MP_P2.00mm_Vertical","C160354"
"PI 5V OUT","J103,J301","USB_C_Receptacle_HRO_TYPE-C-31-M-12","C165948"
"QWIIC PI","J402,J409","JST_SH_BM04B-SRSS-TB_1x04-1MP_P1.00mm_Vertical","C160390"
"3.3uH","L101,L102","IND-SMD_L7.0-W6.6_FXL0630","C167219"
"2N7002","Q201,Q203,Q301,Q302","SOT-23","C8545"
"AOD403","Q101,Q202","TO-252-2","C28969"
"2m 1% 3W 2512","R102","R_2512_6332Metric","C459679"
"22","R309,R310","R_0603_1608Metric","C23345"
"33","R502,R503","R_0603_1608Metric","C23140"
"100","R209","R_0603_1608Metric","C22775"
"330","R408,R409,R410","R_0603_1608Metric","C23138"
"1k","R114,R204,R303,R304,R316,R401,R402,R404,R604,R605,R704,R705,R804,R805,R904,R905","R_0603_1608Metric","C21190"
"1.8k","R601,R701,R801,R901","R_0603_1608Metric","C4177"
"2.2k","R314,R315","R_0603_1608Metric","C4190"
"3k","R107,R110","R_0603_1608Metric","C4211"
"4.7k","R208,R210,R312,R313","R_0603_1608Metric","C23162"
"5.1k","R307,R308","R_0603_1608Metric","C23186"
"10k","R101,R103,R112,R113,R207,R211,R213,R301,R302,R311,R403,R405,R406,R407,R602,R603,R702,R703,R802,R803,R902,R903","R_0603_1608Metric","C25804"
"20k","R105,R108,R111","R_0603_1608Metric","C4184"
"22k","R106,R109","R_0603_1608Metric","C31850"
"33k","R212","R_0603_1608Metric","C4216"
"47k","R201","R_0603_1608Metric","C25819"
"100k","R104,R202,R203,R205,R206,R305,R306","R_0603_1608Metric","C25803"
"470k","R501","R_0603_1608Metric","C23178"
"4x10k","RN401,RN402","R_Array_Convex_4x0603","C29718 C20197"
"BOOT","SW302","SW-SMD_L3.9-W3.0-P4.45","C720477"
"RESET","SW301","SW-SMD_L3.9-W3.0-P4.45","C720477"
"74HCT125D","U401","SOIC-14_3.9x8.7mm_P1.27mm","C5962"
"74LVC1G123DC (JSM)","U201","VSSOP-8_2.3x2mm_P0.5mm","C53114387"
"AMS1117-3.3","U104","SOT-223-3_TabPin2","C6186"
"DRV8874PWPR","U601,U701,U801,U901","HTSSOP-16-1EP_4.4x5mm_P0.65mm_EP3.4x5mm_Mask2.46x2.31mm","C1855818"
"ESP32-S3-WROOM-1-N16R2","U301","WIRELM-SMD_ESP32-S3-WROOM-1","C2913205"
"INA226AIDGSR","U101","MSOP-10_3x3mm_P0.5mm","C49851"
"MAX98357AETE+T","U501","TQFN-16-1EP_3x3mm_P0.5mm_EP1.23x1.23mm","C910544"
"SRV05-4","U302","SOT-23-6","C85364"
"TCA9555PWR","U303","TSSOP-24_4.4x7.8mm_P0.65mm","C465732"
"TPS56637RPAR","U102,U103","VQFN-HR-10_L3.0-W3.0_RPA","C841386"

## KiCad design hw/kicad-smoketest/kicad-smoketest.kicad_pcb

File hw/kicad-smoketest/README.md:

# KiCad smoke test

A tiny 20 x 15 mm board that proves the headless KiCad pipeline on the VPS works end to end, before the real Super bot PCBs.

Circuit: 2-pin header (VIN, GND) -> 1k resistor -> red LED -> GND.

| Ref | Part | Footprint | LCSC | JLC type |
|-----|------|-----------|------|----------|
| R1 | 1k 1% 0603 (UNI-ROYAL 0603WAF1001T5E) | Resistor_SMD:R_0603_1608Metric | C21190 | Basic |
| D1 | Red LED 0603 (KENTO KT-0603R) | LED_SMD:LED_0603_1608Metric | C2286 | Basic |
| J1 | 1x02 2.54 mm pin header (BOOMELE B-2100S02P-A110) | PinHeader_1x02_P2.54mm_Vertical | C124375 | Extended, through-hole |

J1 is through-hole and there is no Basic 1x2 header, so for a real order leave it out of assembly and hand-solder it, or pay for THT assembly.

## How it was made

Everything went through the `kicad` MCP server (mixelpixx/KiCAD-MCP-Server v2.9.0), driven by an MCP client on the VPS:

1. `create_project`, `batch_add_and_connect` (3 parts + nets), `set_schematic_component_property` (LCSC fields), `run_erc`
2. `open_board`, `sync_schematic_to_board`, `add_board_outline` (rounded 20x15), `set_design_rules`, `move_component` x3, `save_board`
3. `autoroute` (Freerouting 2.5.0 on Java 25, 4.6 s, 5 tracks, 0 vias), `run_drc`
4. MCP export tools (`export_gerbers`, `export_drill`, `export_pos`, `export_3d_cli`, `get_board_2d_view`) were checked too

Then the helper scripts (see docs/kicad-setup.md) made the committed outputs:

- `kicad-check kicad-smoketest.kicad_pcb`: ERC 0, DRC 0 violations, 0 unconnected, 0 schematic-parity issues (reports in `reports/`)
- `kicad-jlc .`: KiBot 1.9.1 with its built-in JLCPCB preset (`jlcpcb.kibot.yaml`)
- `kicad-render kicad-smoketest.kicad_pcb`: the PNG/SVG/PDF/STEP files in `renders/`

## Files

- `out/JLCPCB/kicad-smoketest-_JLCPCB_compress.zip`: Gerbers + drill files, ready to upload to JLCPCB
- `out/fab/jlcpcb/kicad-smoketest_bom_jlc.csv`: BOM (Comment, Designator, Footprint, LCSC Part #)
- `out/fab/jlcpcb/kicad-smoketest_cpl_jlc.csv`: CPL / pick-and-place (Designator, Mid X, Mid Y, Rotation, Layer)
- `out/3d/kicad-smoketest-3D.step` and `renders/kicad-smoketest.step`: 3D model
- `out/docs/kicad-smoketest-schematic.pdf`, `out/*-erc.html`, `out/*-drc.html`
- `renders/pcb-3d-top.png`, `pcb-3d-bottom.png`, `pcb-3d-iso.png`: ray-traced 3D renders
- `renders/pcb-front.png`, `pcb-back.png`: 2D copper/silk/mask plots
- `renders/kicad-smoketest.png`: schematic

Nothing was ordered. Check JLCPCB rotation offsets in their preview before a real order, since KiCad and JLC footprints sometimes disagree.

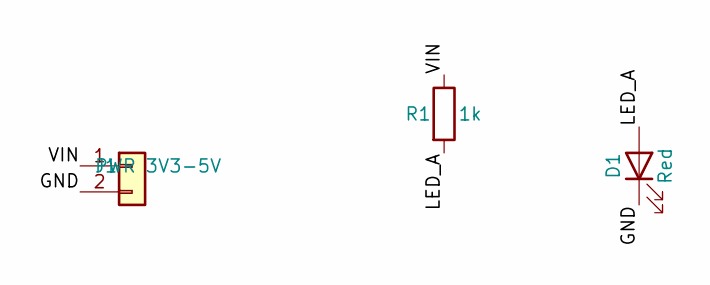
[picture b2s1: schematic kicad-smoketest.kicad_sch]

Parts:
D1: Red; LED_0603_1608Metric; LCSC C2286
J1: PWR 3V3-5V; PinHeader_1x02_P2.54mm_Vertical; LCSC C124375
R1: 1k; R_0603_1608Metric; LCSC C21190

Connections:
/GND: D1.1 (K), J1.2
/LED_A: D1.2 (A), R1.2
/VIN: J1.1, R1.1

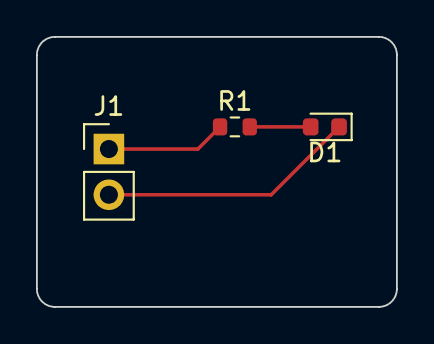
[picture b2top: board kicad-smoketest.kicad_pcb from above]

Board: 2 copper layers, 20.0 x 15.0 mm, 3 parts (0 on the bottom side), 3 nets.
